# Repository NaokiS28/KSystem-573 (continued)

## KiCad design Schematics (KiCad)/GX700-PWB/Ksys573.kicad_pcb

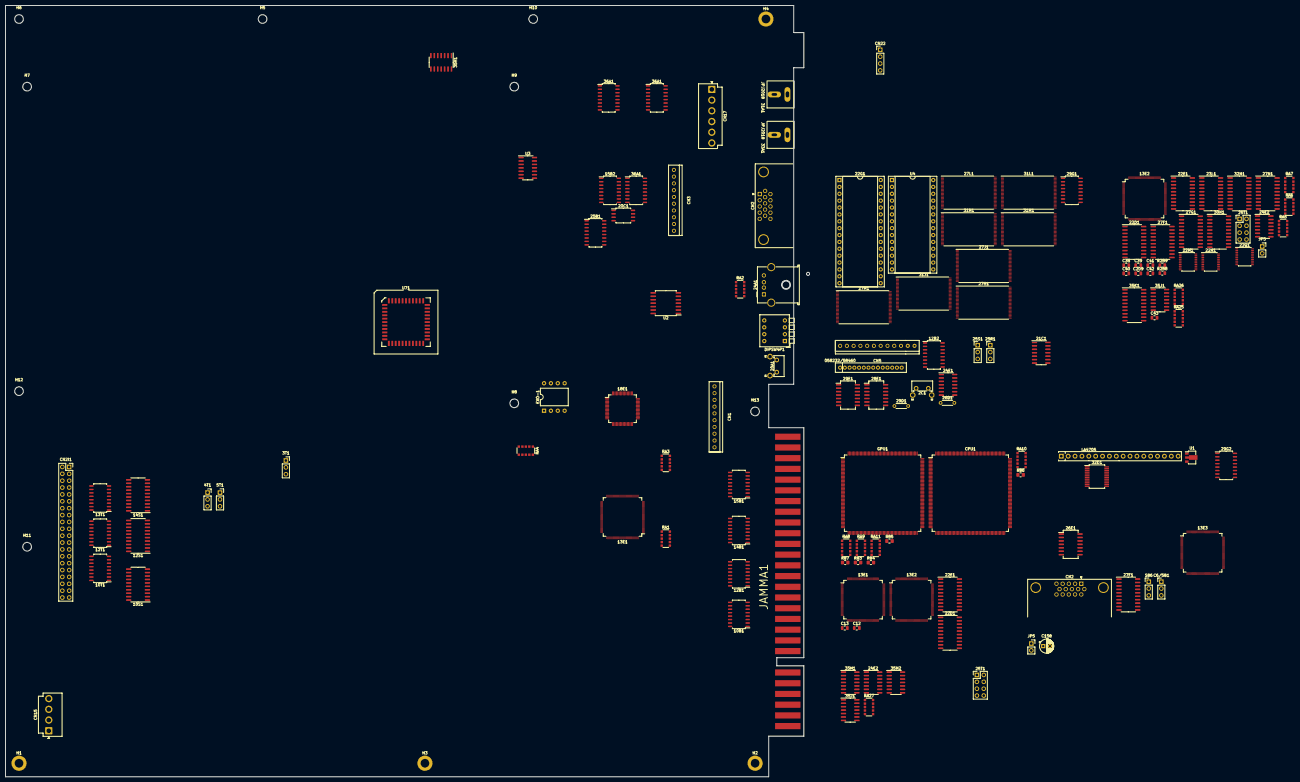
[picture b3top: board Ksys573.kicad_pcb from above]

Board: 4 copper layers, 295.0 x 285.0 mm, 145 parts (0 on the bottom side), 416 nets, no tracks yet.

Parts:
2C1: EVQ-PC1; SW_Tactile_SPST_Angled_PTS645Vx58-2LFS
3T1, 4T1, 5T1: EMI_Filter_LCL; PinSocket_1x03_P2.54mm_Vertical
10B1, 10T1, 12B1, 12B2, 12T1, 13T1, 14B1, 15B1, 15B2, 25B1, 36A1, 36A1#2, 36A1#3: ZBDS5101-8PT; SOIC-16_4.55x10.3mm_P1.27mm
10S1, 12S1, 14S1: 74LS245; SO-20_5.3x12.6mm_P1.27mm
13E1, 13E1#2, 13E2, 13E2#2, 13E3: KONAMI_056879; TQFP-120_14x14mm_P0.4mm
18E1: HD6433640; TQFP-64_10x10mm_P0.5mm
20A1: SW_Push; SW_Tactile_SPST_Angled_PTS645Vx58-2LFS
20C1: MAX485E; SOIC-8_5.23x5.23mm_P1.27mm
21C1, 35J1#2: 74LS74; SO-14_3.9x8.65mm_P1.27mm
22D1, 22D1#2, 22E1, 22E1#2, 27F1, 27F1#2, 27G1, 35K1: 74LS273; SO-20_5.3x12.6mm_P1.27mm
22G1: 27C040; DIP-32_W15.24mm_Socket
22M1, 22N1, 22Q1: 74LCX245; SSOP-20_4.4x6.5mm_P0.65mm
23L1, 27N1, 30N1, 32N1: 74F245; SO-20_5.3x12.6mm_P1.27mm
24A1: USB_A; USB_A_Molex_67643_Horizontal
24E1, 24E2, 24E2#2: 74LS14; SO-14_3.9x8.65mm_P1.27mm
25R1: U102; PinHeader_1x03_P2.54mm_Vertical
25S1: U101; PinHeader_1x03_P2.54mm_Vertical
25T1, 25T1#2: S240; PinHeader_2x04_P2.54mm_Vertical
26D1, 29D1: ZBF503D-00; R_Axial_DIN0204_L3.6mm_D1.6mm_P5.08mm_Horizontal
26E1: 74LS74; SO-14_5.3x10.2mm_P1.27mm
27H1, 27J1, 27L1, 27M1, 31H1, 31J1, 31L1, 31M1: 29F016-TSOP-SP; TSOP-I-48_18.4x12mm_P0.5mm
28E1, 29E1: 74LS07; SO-14_5.3x10.2mm_P1.27mm
29G1, 29G2: 74LS139; SOIC-16_4.55x10.3mm_P1.27mm
31A1: LINE L-OUT; RCA
32D1: SM5877AM; SSOP-24_5.3x8.2mm_P0.65mm
33A1: LINE R-OUT; RCA
35H1, 35H1#2, 35H2, 35J1: 74LS125; SO-14_3.9x8.65mm_P1.27mm
058232/58460: KONAMI-058232; KONAMI-SIP-14
C6/5B1: EMI222; PinHeader_1x03_P2.54mm_Vertical
C12, C13, C38, C39, C40, C41, C42, C43, C209: 10n; C_0805_2012Metric
C158: 10M16E; CP_Radial_D5.0mm_P2.50mm
CN1, CN3: B10PSHF1A; JST_NH_B10P_SHD
CN2, CN2#2: VGA-DSUB15; DSUB-15-HD_Female_Horizontal_P2.29x1.98mm_EdgePinOffset8.35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
CN2I1: ATA-IDE; PinSocket_2x20_P2.54mm_Vertical
CN5: B12PSHF1A; JST_NH_B12P_SHD
CN15: B4P-VH; JST_VH_B4P-VH-B_1x04_P3.96mm_Vertical
CN17: B6P-VH; JST_VH_B6P-VH-B_1x06_P3.96mm_Vertical
CN22: BS4PSHF1AA; PinHeader_1x04_P2.54mm_Vertical
CPU1: CXD8530CQ; LQFP-208_28x28mm_P0.5mm
DIPSW4P1: SW_DIP_x04; SW_DIP_SPSTx04_Piano_10.8x11.72mm_W7.62mm_P2.54mm
EXO-1: 14.7456MHz; DIP-8_W10.16mm
GPU1: CXD8561CQ; LQFP-208_28x28mm_P0.5mm
H1, H2, H3, H4: MountingHole_Pad; MountingHole_3.2mm_M3_DIN965_Pad
H5, H6, H7, H8, H9, H10, H11, H12, H13: MountingHole; MountingHole_3.2mm_M3
JAMMA1: JAMMA
JP5, JP5#2: Jumper_NO_Small; PinSocket_1x02_P2.54mm_Vertical
LA4705: LA4705; SIP18_Housing
R83, R84, R85, R86, R87: 220; R_0805_2012Metric_Pad1.20x1.40mm_HandSolder
R288: 100; R_0805_2012Metric
R289: 470; R_0805_2012Metric
RA1, RA2, RA3, RA4: 2.2k; R_Array_Convex_5x1206
RA5, RA6, RA7, RA25, RA26, RA27: 4.7k; R_Array_Convex_5x1206
RA8, RA9, RA10, RA11: 472; R_Array_Convex_5x1206
S86: Conn_01x03; PinHeader_1x03_P2.54mm_Vertical
U1: L78L05_SOT89; SOT-89-3
U2: ADC0834; SOIC-14W_7.5x9mm_P1.27mm
U3: 74LS74; SO-14_3.9x8.65mm_P1.27mm
U4: M48T58Y; DIP-28_W15.24mm_Socket
U71: 22J-X700A1 XC9536; PLCC-44_SMD-Socket

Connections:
13E-59: 13E1.59, 13E1#2.59
13E-PIN17: 13E1.17, 13E3.17
18E-17: 13E1.49, 13E1#2.49, 18E1.17 (P60)
18E-18: 13E1.50, 13E1#2.50, 18E1.18 (P61)
18E-34: 18E1.34 (P73), 21C1.5 (Q)
18E-35: 13E3.95, 18E1.35 (P74/TMRIV), 21C1.9 (Q)
18E-36: 13E3.96, 18E1.36 (P75/TMCIV)
18E-54: 18E1.54 (P14/PWM), 21C1.11 (C)
21C-1: 18E1.53 (P10/TMOW), 21C1.1 (~R)
22D-2: 18E1.39 (P80/FTCI), 22D1.2, 22D1#2.2 (Q0)
22D-5: 18E1.40 (P81/FTOA), 22D1.5, 22D1#2.5 (Q1)
22D-6: 18E1.41 (P82/FTOB), 22D1.6, 22D1#2.6 (Q2)
22D-9: 18E1.42 (P83/FTIA), 22D1.9, 22D1#2.9 (Q3)
22D-12: 18E1.43 (P84/FTIB), 22D1.12, 22D1#2.12 (Q4)
22D-15: 18E1.44 (P85/FTIC), 22D1.15, 22D1#2.15 (Q5)
22D-16: 18E1.45 (P86/FTID), 22D1.16, 22D1#2.16 (Q6)
22D-19: 18E1.46 (P87), 22D1.19, 22D1#2.19 (Q7)
22E-2: 18E1.1 (PB1/AN1), 22E1.2, 22E1#2.2 (Q0)
22E-5: 18E1.2 (PB0/AN0), 22E1.5, 22E1#2.5 (Q1)
22E-6: 18E1.64 (PB2/AN2), 22E1.6, 22E1#2.6 (Q2)
22E-9: 18E1.63 (PB3/AN3), 22E1.9, 22E1#2.9 (Q3)
22E-12: 18E1.62 (PB4/AN4), 22E1.12, 22E1#2.12 (Q4)
22E-15: 18E1.61 (PB5/AN5), 22E1.15, 22E1#2.15 (Q5)
22E-16: 18E1.60 (PB6/AN6), 22E1.16, 22E1#2.16 (Q6)
22E-19: 18E1.59 (PB7/AN7), 22E1.19, 22E1#2.19 (Q7)
22M-13: 25T1.4, 25T1.5, 25T1#2.4, 25T1#2.5
24E-13: 24E2.13, 24E2#2.13, 27G1.16 (Q6)
25T-6: 25T1.3, 25T1.6
25T-7: 25T1.2, 25T1.7
25T-8: 25T1.1, 25T1.8
27G-2: 27G1.2 (Q0), 29G1.14
27G-5: 27G1.5 (Q1), 29G1.13
27G-12: 27G1.12 (Q4), 29G1.2, 29G2.2 (A0)
27G-15: 27G1.15 (Q5), 29G1.3, 29G2.3 (A1)
29G-5: 29G1.5, 29G2.5 (O1)
29G-6: 25R1.2, 25R1.3, 29G1.6, 29G2.6 (O2)
35J-5: 13E3.97, 35J1#2.5 (Q)
35J-9: 13E3.98, 35J1#2.9 (Q), RA26.6 (R5)
058232-4: 13E1.83, 13E3.84, 058232/58460.4 (CC-IN2)
058232-5: 13E1.84, 13E3.85, 058232/58460.5 (CC-IN1)
+3V3: 22M1.20 (VCC), 22N1.20 (VCC), 22Q1.20 (VCC), RA8.5 (common), RA8.10 (common), RA9.5 (common), RA9.10 (common), RA10.5 (common), RA10.10 (common), RA11.5 (common), RA11.10 (common)
+5V: 13E1.16, 13E1.46, 13E1.60, 13E1.85, 13E1.120, 13E2.106, 22D1.20, 22E1.20, 27F1.20, 35J1.12, C41.1, C42.1
+12V: 3T1.1, 058232/58460.1 (COINC-FB), CN17.5, CN17.6
/IDE/IDE-A0: 13T1.14, CN2I1.35
/IDE/IDE-A1: 13T1.12, CN2I1.33
/IDE/IDE-A2: 13T1.13, CN2I1.36
/IDE/IDE-D0: 12T1.10, CN2I1.17
/IDE/IDE-D1: 12T1.12, CN2I1.15
/IDE/IDE-D2: 12T1.14, CN2I1.13
/IDE/IDE-D3: 12T1.16, CN2I1.11
/IDE/IDE-D4: 10T1.10, CN2I1.9
/IDE/IDE-D5: 10T1.12, CN2I1.7
/IDE/IDE-D6: 10T1.14, CN2I1.5
/IDE/IDE-D7: 10T1.16, CN2I1.3
/IDE/IDE-D8: 10T1.15, CN2I1.4
/IDE/IDE-D9: 10T1.13, CN2I1.6
/IDE/IDE-D10: 10T1.11, CN2I1.8
/IDE/IDE-D11: 10T1.9, CN2I1.10
/IDE/IDE-D12: 12T1.15, CN2I1.12
/IDE/IDE-D13: 12T1.13, CN2I1.14
/IDE/IDE-D14: 12T1.11, CN2I1.16
/IDE/IDE-D15: 12T1.9, CN2I1.18
/IDE/IDE-READ: 13T1.11, CN2I1.25
/IDE/IDE-WRITE: 13T1.10, CN2I1.23
/IO-DATA-0: 13E1.62, 22E1.3, 27F1.3
/IO-DATA-1: 13E1.63, 22E1.4, 27F1.4
/IO-DATA-2: 13E1.64, 22E1.7, 27F1.7
/IO-DATA-3: 13E1.65, 22E1.8, 27F1.8
/IO-DATA-4: 13E1.66, 22E1.13, 27F1.13
/IO-DATA-5: 13E1.67, 22E1.14, 27F1.14
/IO-DATA-6: 13E1.68, 22E1.17, 27F1.17
/IO-DATA-7: 13E1.69, 22E1.18, 27F1.18
/IO-DATA-8: 13E1.10, 22D1.3
/IO-DATA-9: 13E1.72, 22D1.4
/IO-DATA-10: 13E1.73, 22D1.7
/IO-DATA-11: 13E1.74, 22D1.8
/IO-DATA-12: 13E1.75, 22D1.13
/IO-DATA-13: 13E1.76, 22D1.14
/IO-DATA-14: 13E1.77, 22D1.17
/IO-DATA-15: 13E1.78, 22D1.18
/PCCARD (PCMCIA)/IO-AD-0: 25S1.2, 25S1.3
/ROM/IO-ADDR-0: 22G1.12 (A0), 27H1.30 (A0), 27J1.30 (A0), 27L1.30 (A0), 27M1.30 (A0), 31H1.30 (A0), 31J1.30 (A0), 31L1.30 (A0), 31M1.30 (A0)
/ROM/IO-ADDR-1: 22G1.11 (A1), 27H1.29 (A1), 27J1.29 (A1), 27L1.29 (A1), 27M1.29 (A1), 31H1.29 (A1), 31J1.29 (A1), 31L1.29 (A1), 31M1.29 (A1)
/ROM/IO-ADDR-2: 22G1.10 (A2), 27H1.28 (A2), 27J1.28 (A2), 27L1.28 (A2), 27M1.28 (A2), 31H1.28 (A2), 31J1.28 (A2), 31L1.28 (A2), 31M1.28 (A2)
/ROM/IO-ADDR-3: 22G1.9 (A3), 27H1.27 (A3), 27J1.27 (A3), 27L1.27 (A3), 27M1.27 (A3), 31H1.27 (A3), 31J1.27 (A3), 31L1.27 (A3), 31M1.27 (A3)
/ROM/IO-ADDR-4: 22G1.8 (A4), 27H1.22 (A4), 27J1.22 (A4), 27L1.22 (A4), 27M1.22 (A4), 31H1.22 (A4), 31J1.22 (A4), 31L1.22 (A4), 31M1.22 (A4)
/ROM/IO-ADDR-5: 22G1.7 (A5), 27H1.21 (A5), 27J1.21 (A5), 27L1.21 (A5), 27M1.21 (A5), 31H1.21 (A5), 31J1.21 (A5), 31L1.21 (A5), 31M1.21 (A5)
/ROM/IO-ADDR-6: 22G1.6 (A6), 27H1.20 (A6), 27J1.20 (A6), 27L1.20 (A6), 27M1.20 (A6), 31H1.20 (A6), 31J1.20 (A6), 31L1.20 (A6), 31M1.20 (A6)
/ROM/IO-ADDR-7: 22G1.5 (A7), 27H1.19 (A7), 27J1.19 (A7), 27L1.19 (A7), 27M1.19 (A7), 31H1.19 (A7), 31J1.19 (A7), 31L1.19 (A7), 31M1.19 (A7)
/ROM/IO-ADDR-8: 22G1.27 (A8), 27H1.18 (A8), 27J1.18 (A8), 27L1.18 (A8), 27M1.18 (A8), 31H1.18 (A8), 31J1.18 (A8), 31L1.18 (A8), 31M1.18 (A8)
/ROM/IO-ADDR-9: 22G1.26 (A9), 27H1.17 (A9), 27J1.17 (A9), 27L1.17 (A9), 27M1.17 (A9), 31H1.17 (A9), 31J1.17 (A9), 31L1.17 (A9), 31M1.17 (A9)
/ROM/IO-ADDR-10: 22G1.23 (A10), 27H1.16 (A10), 27J1.16 (A10), 27L1.16 (A10), 27M1.16 (A10), 31H1.16 (A10), 31J1.16 (A10), 31L1.16 (A10), 31M1.16 (A10)
/ROM/IO-ADDR-11: 22G1.25 (A11), 27H1.15 (A11), 27J1.15 (A11), 27L1.15 (A11), 27M1.15 (A11), 31H1.15 (A11), 31J1.15 (A11), 31L1.15 (A11), 31M1.15 (A11)
/ROM/IO-ADDR-12: 22G1.4 (A12), 27H1.10 (A12), 27J1.10 (A12), 27L1.10 (A12), 27M1.10 (A12), 31H1.10 (A12), 31J1.10 (A12), 31L1.10 (A12), 31M1.10 (A12)
/ROM/IO-ADDR-13: 22G1.28 (A13), 27H1.9 (A13), 27J1.9 (A13), 27L1.9 (A13), 27M1.9 (A13), 31H1.9 (A13), 31J1.9 (A13), 31L1.9 (A13), 31M1.9 (A13)
/ROM/IO-ADDR-14: 22G1.29 (A14), 27H1.8 (A14), 27J1.8 (A14), 27L1.8 (A14), 27M1.8 (A14), 31H1.8 (A14), 31J1.8 (A14), 31L1.8 (A14), 31M1.8 (A14)
/ROM/IO-ADDR-15: 22G1.3 (A15), 27H1.7 (A15), 27J1.7 (A15), 27L1.7 (A15), 27M1.7 (A15), 31H1.7 (A15), 31J1.7 (A15), 31L1.7 (A15), 31M1.7 (A15)
/ROM/IO-ADDR-16: 22G1.2 (A16), 27H1.6 (A16), 27J1.6 (A16), 27L1.6 (A16), 27M1.6 (A16), 31H1.6 (A16), 31J1.6 (A16), 31L1.6 (A16), 31M1.6 (A16)
/ROM/IO-ADDR-17: 22G1.30 (A17), 27H1.5 (A17), 27J1.5 (A17), 27L1.5 (A17), 27M1.5 (A17), 31H1.5 (A17), 31J1.5 (A17), 31L1.5 (A17), 31M1.5 (A17)
/ROM/IO-ADDR-18: 22G1.31 (A18), 27H1.4 (A18), 27J1.4 (A18), 27L1.4 (A18), 27M1.4 (A18), 31H1.4 (A18), 31J1.4 (A18), 31L1.4 (A18), 31M1.4 (A18)
/ROM/IO-ADDR-19: 27H1.3 (A19), 27J1.3 (A19), 27L1.3 (A19), 27M1.3 (A19), 31H1.3 (A19), 31J1.3 (A19), 31L1.3 (A19), 31M1.3 (A19)
/ROM/IO-ADDR-20: 27H1.46 (A20), 27J1.46 (A20), 27L1.46 (A20), 27M1.46 (A20), 31H1.46 (A20), 31J1.46 (A20), 31L1.46 (A20), 31M1.46 (A20)
/ROM/IO-DATA-0: 22G1.13 (D0), 31H1.31 (D0), 31J1.31 (D0), 31L1.31 (D0), 31M1.31 (D0), U4.11 (DQ0)
/ROM/IO-DATA-1: 22G1.14 (D1), 31H1.32 (D1), 31J1.32 (D1), 31L1.32 (D1), 31M1.32 (D1), U4.12 (DQ1)
/ROM/IO-DATA-2: 22G1.15 (D2), 31H1.33 (D2), 31J1.33 (D2), 31L1.33 (D2), 31M1.33 (D2), U4.13 (DQ2)
/ROM/IO-DATA-3: 22G1.17 (D3), 31H1.34 (D3), 31J1.34 (D3), 31L1.34 (D3), 31M1.34 (D3), U4.15 (DQ3)
/ROM/IO-DATA-4: 22G1.18 (D4), 31H1.38 (D4), 31J1.38 (D4), 31L1.38 (D4), 31M1.38 (D4), U4.16 (DQ4)
/ROM/IO-DATA-5: 22G1.19 (D5), 31H1.39 (D5), 31J1.39 (D5), 31L1.39 (D5), 31M1.39 (D5), U4.17 (DQ5)
/ROM/IO-DATA-6: 22G1.20 (D6), 31H1.40 (D6), 31J1.40 (D6), 31L1.40 (D6), 31M1.40 (D6), U4.18 (DQ6)
/ROM/IO-DATA-7: 22G1.21 (D7), 31H1.41 (D7), 31J1.41 (D7), 31L1.41 (D7), 31M1.41 (D7), U4.19 (DQ7)
/ROM/IO-DATA-8: 27H1.31 (D0), 27J1.31 (D0), 27L1.31 (D0), 27M1.31 (D0)
/ROM/IO-DATA-9: 27H1.32 (D1), 27J1.32 (D1), 27L1.32 (D1), 27M1.32 (D1)
/ROM/IO-DATA-10: 27H1.33 (D2), 27J1.33 (D2), 27L1.33 (D2), 27M1.33 (D2)
/ROM/IO-DATA-11: 27H1.34 (D3), 27J1.34 (D3), 27L1.34 (D3), 27M1.34 (D3)
/ROM/IO-DATA-12: 27H1.38 (D4), 27J1.38 (D4), 27L1.38 (D4), 27M1.38 (D4)
/ROM/IO-DATA-13: 27H1.39 (D5), 27J1.39 (D5), 27L1.39 (D5), 27M1.39 (D5)
/ROM/IO-DATA-14: 27H1.40 (D6), 27J1.40 (D6), 27L1.40 (D6), 27M1.40 (D6)
/ROM/IO-DATA-15: 27H1.41 (D7), 27J1.41 (D7), 27L1.41 (D7), 27M1.41 (D7)
/Security Cart/CART-7.37MHz: 35H1.3, 35H1#2.3
/Security Cart/CART-RTS: 35H1.11, 35H1#2.11
ADC-CLK: 13E1.80, 13E3.83, U2.12 (CLK)
ADC-DIN: 13E1.79, 13E3.79, U2.13 (DIN)
ADC-DOUT: 13E1.89, 13E3.89, U2.10 (DOUT)
ADC-SARS: 13E1.92, 13E3.80, 13E3.92, U2.11 (SARS)
ADC-~CS: 13E1.82, 13E3.82, U2.2 (~CS)
BUS-~RD: 10S1.1 (A->B), 12S1.1 (A->B), U4.22 (~OE), U71.18 (M13)
BUS-~WR: 27H1.44 (~WE), 27J1.44 (~WE), 27L1.44 (~WE), 27M1.44 (~WE), 31H1.44 (~WE), 31J1.44 (~WE), 31L1.44 (~WE), 31M1.44 (~WE), U4.27 (~WR), U71.25 (M17)
CART-20: 35H1.9, 35H2.9, 35K1.2 (Q0), RA25.9 (R8)
CART-29: 35J1#2.3 (C), RA26.4 (R4)
CART-30: 35J1.13, 35J1#2.13 (~R), RA26.7 (R6)
CART-33: 13E2.38, 13E2#2.38, RA27.1 (R1)
CART-34: 13E2.37, 13E2#2.37, RA27.2 (R2)
CART-35: 13E2.36, 13E2#2.36, RA27.3 (R3)
CART-36: 13E2.35, 13E2#2.35, RA27.4 (R4)
CART-37: 13E2.34, 13E2#2.34, RA27.9 (R8)
CART-38: 13E2.33, 13E2#2.33, RA27.8 (R7)
CART-39: 13E2.32, 13E2#2.32, RA27.7 (R6)
CART-40: 13E1.30, 13E1#2.30, RA27.6 (R5)
CN21-B6: 23L1.17 (B1), JP5.1, JP5#2.1
COIN1IN: 13E1.6, 13E3.6, RA1.2 (R2)
COIN2IN: 13E1.7, 13E3.7, RA1.8 (R7)
COIN-CNT1: 10B1.16, 058232/58460.3 (CC-OUT1)
COIN-CNT2: 10B1.15, 058232/58460.2 (CC-OUT2)
DAC-MUTE: 13E1.87, 13E3.87
DIP-1: 13E1.22, 13E1#2.22, DIPSW4P1.8
DIP-2: 13E1.23, 13E1#2.23, DIPSW4P1.7
DIP-3: 13E1.24, 13E1#2.24, DIPSW4P1.6
DIP-4: 13E1.25, 13E1#2.25, DIPSW4P1.5
DREQ5: 22M1.12 (B6), 25T1#2.3, 25T1#2.6
EXO-CLK: 18E1.8 (OSC1), 35H1.2, 35H1#2.2, EXO-1.2 (D)
EXP-A10: 13E1.90, 22D1.1, 22E1.1
EXT-OUT-LATCH: 27F1#2.11 (Cp), U71.43 (M4)
FLASH-CE0: 27H1.11 (~CE), 29G1.9, 31H1.11 (~CE)
FLASH-CE1: 27J1.11 (~CE), 29G1.10, 31J1.11 (~CE)
FLASH-CE2: 29G1.11, 31L1.11 (~CE)
FLASH-CE3: 27M1.11 (~CE), 29G1.12, 31M1.11 (~CE)
GND: 2C1.2, 3T1.2, 4T1.1, 4T1.2, 5T1.2, 10B1.13, 10S1.10 (GND), 12S1.10 (GND), 13E1.1, 13E1.11, 13E1.21, 13E1.41, 13E1.61, 13E1.71, 13E1.81, 13E1.91, 13E1.111, 13E1#2.21, 13E1#2.41, 13E1#2.51, 13E2.31, 13E2.101, 13E2#2.31, 13E3.1, 13E3.11, 13E3.61, 13E3.71, 13E3.81, 13E3.91, 13E3.101, 13E3.111, 14S1.10 (GND), 14S1.19 (CE), 15B1.9, 15B1.13, 15B2.9, 15B2.13, 18E1.3 (AVSS), 18E1.4 (TEST), 18E1.5 (X2), 18E1.7 (VSS), 20A1.2, 20C1.5 (GND), 22D1.10, 22D1#2.10 (GND), 22E1.10, 22E1#2.10 (GND), 22G1.16 (GND), 22G1.22 (~CE), 22M1.1 (A->B), 22M1.10 (GND), 22M1.17 (B1), 22M1.18 (B0), 22M1.19 (CE), 22N1.10 (GND), 22Q1.10 (GND), 23L1.10 (GND), 23L1.19 (CE), 25B1.9, 25B1.12, 25B1.16, 27F1.10, 27F1#2.10 (GND), 27G1.10 (GND), 27H1.35 (GND), 27H1.36 (GND), 27J1.35 (GND), 27J1.36 (GND), 27L1.35 (GND), 27L1.36 (GND), 27M1.35 (GND), 27M1.36 (GND), 27N1.10 (GND), 27N1.19 (CE), 29D1.1, 30N1.10 (GND), 30N1.19 (CE), 31H1.35 (GND), 31H1.36 (GND), 31J1.35 (GND), 31J1.36 (GND), 31L1.35 (GND), 31L1.36 (GND), 31M1.35 (GND), 31M1.36 (GND), 32N1.10 (GND), 32N1.19 (CE), 35H1.1, 35H1.4, 35H1.13, 35H1#2.1, 35H1#2.4, 35H1#2.13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
H8-TX-FLAG: 21C1.3 (C), U71.39 (I/O/GSR)
IDE-CS0: 13T1.15, 14S1.8 (A6), CN2I1.37, U71.2 (M1)
IDE-CS1: 13T1.16, 14S1.9 (A7), CN2I1.38, U71.3 (M2)
IDE-~RST: 14S1.2 (A0), 26E1.5 (Q)
IO-ADDR-0: 32N1.18 (B0), RA5.6 (R5)
IO-ADDR-1: 13E2.103, 13E3.103, 14S1.7 (A5), 32N1.17 (B1), RA5.4 (R4)
IO-ADDR-2: 13E2.104, 13E3.104, 14S1.5 (A3), 32N1.16 (B2), RA5.7 (R6)
IO-ADDR-3: 13E2.105, 13E3.105, 14S1.6 (A4), 32N1.15 (B3), RA5.3 (R3)
IO-ADDR-4: 32N1.14 (B4), RA5.8 (R7)
IO-ADDR-5: 32N1.13 (B5), RA5.2 (R2)
IO-ADDR-6: 32N1.12 (B6), RA5.9 (R8)
IO-ADDR-7: 32N1.11 (B7), RA5.1 (R1)
IO-ADDR-9: 30N1.17 (B1), RA6.4 (R4)
IO-ADDR-10: 5T1.1, 10S1.20 (VCC), 12S1.20 (VCC), 13E1#2.46, 13E1#2.60, 13E3.16, 13E3.99, 13E3.106, 13E3.120, 14S1.1 (A->B), 14S1.20 (VCC), 15B1.15, 15B1.16, 18E1.6 (X1), 18E1.33 (VCC), 18E1.58 (AVCC), 20C1.8 (VCC), 21C1.2 (D), 21C1.4 (~S), 21C1.10 (~S), 21C1.12 (D), 22D1#2.20 (VCC), 22E1#2.20 (VCC), 22G1.1 (VPP), 22G1.32 (VCC), 23L1.1 (A->B), 23L1.20 (VCC), 25B1.11, 26D1.1, 26E1.4 (~S), 26E1.10 (~S), 27F1#2.20 (VCC), 27G1.20 (VCC), 27H1.12 (VCC), 27H1.37 (VCC), 27J1.12 (VCC), 27J1.37 (VCC), 27L1.12 (VCC), 27L1.37 (VCC), 27M1.12 (VCC), 27M1.37 (VCC), 27N1.1 (A->B), 27N1.20 (VCC), 30N1.1 (A->B), 30N1.16 (B2), 30N1.18 (B0), 30N1.20 (VCC), 31H1.12 (VCC), 31H1.37 (VCC), 31J1.12 (VCC), 31J1.37 (VCC), 31L1.12 (VCC), 31L1.37 (VCC), 31M1.12 (VCC), 31M1.37 (VCC), 32N1.1 (A->B), 32N1.20 (VCC), 35J1#2.2 (D), 35J1#2.4 (~S), 35J1#2.10 (~S), 35J1#2.12 (D), 35K1.20 (VCC), C6/5B1.1, C12.1, C13.1, C38.1, C39.1, C40.1, C43.1, C209.1, CN1.1, CN1.2, CN3.1, CN3.2, CN17.1, CN17.2, CN22.3, EXO-1.3 (ST), EXO-1.8 (VCC), R289.1, RA1.5 (common), RA1.10 (common), RA2.5 (common), RA2.10 (common), RA3.5 (common), RA3.10 (common), RA4.5 (common), RA5.5 (common), RA5.10 (common), RA6.5 (common), RA6.6 (R5), RA6.7 (R6), RA6.10 (common)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
IO-ADDR-11: 30N1.15 (B3), RA6.3 (R3)
IO-ADDR-12: 30N1.14 (B4), RA6.8 (R7)
IO-ADDR-13: 30N1.13 (B5), RA6.2 (R2)
IO-ADDR-14: 30N1.12 (B6), RA6.9 (R8)
IO-ADDR-15: 30N1.11 (B7), RA6.1 (R1)
IO-ADDR-16: 27N1.18 (B0), RA7.6 (R5)
IO-ADDR-17: 27N1.17 (B1), RA7.4 (R4)
IO-ADDR-18: 27N1.16 (B2), RA7.7 (R6), U71.14 (M12)
IO-ADDR-19: 27N1.15 (B3), RA7.3 (R3), U71.13 (M11)
IO-ADDR-20: 27N1.14 (B4), RA7.8 (R7), U71.12 (M10)
IO-ADDR-21: 27N1.13 (B5), RA7.2 (R2), U71.11 (M9)
IO-ADDR-22: 27N1.12 (B6), RA7.9 (R8), U71.9 (M8)
IO-ADDR-23: 27N1.11 (B7), RA7.1 (R1), U71.8 (M6)
IO-DATA-0: 12S1.8 (A6), 13E3.62, 22N1.18 (B0), 26E1.2 (D), 27F1#2.3 (D0), 27G1.3 (D0), 35K1.3 (D0)
IO-DATA-1: 13E3.63, 22N1.17 (B1), 27F1#2.4 (D1), 27G1.4 (D1), 35K1.4 (D1)
IO-DATA-2: 13E3.64, 22N1.16 (B2), 27F1#2.7 (D2), 27G1.7 (D2), 35K1.7 (D2)
IO-DATA-3: 13E3.65, 22N1.15 (B3), 27F1#2.8 (D3), 27G1.8 (D3), 35K1.8 (D3)
IO-DATA-4: 13E3.66, 22N1.14 (B4), 27F1#2.13 (D4), 27G1.13 (D4), 35K1.13 (D4)
IO-DATA-5: 13E3.67, 22N1.13 (B5), 27F1#2.14 (D5), 27G1.14 (D5), 35K1.14 (D5)
IO-DATA-6: 13E3.68, 22N1.12 (B6), 27F1#2.17 (D6), 27G1.17 (D6), 35K1.17 (D6)
IO-DATA-7: 13E3.69, 22N1.11 (B7), 27F1#2.18 (D7), 27G1.18 (D7), 35K1.18 (D7)
IO-DATA-8: 13E3.10 (70), 22D1#2.3 (D0), 22Q1.18 (B0), 26E1.12 (D)
IO-DATA-9: 13E3.72, 22Q1.17 (B1)
IO-DATA-10: 13E3.73, 22Q1.16 (B2)
IO-DATA-11: 13E3.74, 22Q1.15 (B3)
IO-DATA-12: 13E3.75, 22Q1.14 (B4)
IO-DATA-13: 13E3.76, 22Q1.13 (B5)
IO-DATA-14: 13E3.77, 22Q1.12 (B6)
IO-DATA-15: 13E3.78, 22Q1.11 (B7)
J1-B4: 15B2.1, CN1.3, JAMMA1.A24 (P1_B4)
J1-B5: 15B2.2, CN1.4, JAMMA1.A25 (P1_B5)
J2-B4: 15B2.5, CN1.7, JAMMA1.B24 (P2_B4)
J2-B5: 15B2.7, CN1.9, JAMMA1.B25 (P2_B5)
JVS-RTS: 18E1.47 (P20/SCK3), 20C1.2 (~RE), 20C1.3 (DE)
JVS-RX: 18E1.48 (P21/RXD), 20C1.1 (RO)
JVS-S-IN: 13E1.94, 13E3.94, 18E1.11 (P90/FVPP), 24E1.10
JVS-SENSE: 24E1.9, 25B1.15
JVS-TX: 18E1.49 (P22/TXD), 20C1.4 (DI)
KCUS-93: 13E3.93, 35H2.8
LINE-L: 36A1.15, 36A1#2.15, 36A1#3.15
LINE-R: 36A1.13, 36A1#2.13, 36A1#3.13
LS273-~RST: 27F1.1, 27F1#2.1 (~Mr), 27G1.1 (~Mr)
unnamed: JAMMA1.A1 (GND), JAMMA1.A2 (GND), JAMMA1.A26 (GND), JAMMA1.A27 (GND), JAMMA1.B1 (GND), JAMMA1.B2 (GND), JAMMA1.B26 (GND), JAMMA1.B27 (GND)
unnamed: 3T1.3, CN15.1
unnamed: JAMMA1.A3 (+5V), JAMMA1.A4 (+5V), JAMMA1.B3 (+5V), JAMMA1.B4 (+5V)
unnamed: 4T1.3, CN15.2, CN15.3
unnamed: JAMMA1.A5 (-5V), JAMMA1.B5 (-5V)
unnamed: 5T1.3, CN15.4
unnamed: JAMMA1.A6 (+12V), JAMMA1.B6 (+12V)
unnamed: 10B1.1, JAMMA1.A7 (COIN_COUNT1)
unnamed: 10B1.2, JAMMA1.B7 (COIN_COUNT2)
unnamed: 10B1.4, JAMMA1.A13 (VIDEO-GND)
unnamed: 10B1.5, JAMMA1.A14 (TEST)
unnamed: 10B1.6, JAMMA1.B13 (SERVICE)
unnamed: 10B1.7, JAMMA1.A15 (COIN_1)
unnamed: 10B1.8, JAMMA1.B15 (COIN_2)
unnamed: 10S1.11 (B7), 10T1.8
unnamed: 10S1.12 (B6), 10T1.7
unnamed: 10S1.13 (B5), 10T1.6
unnamed: 10S1.14 (B4), 10T1.5
unnamed: 10S1.15 (B3), 10T1.4
unnamed: 10S1.16 (B2), 10T1.3
unnamed: 10S1.17 (B1), 10T1.2
unnamed: 10S1.18 (B0), 10T1.1
unnamed: 12B1.1, JAMMA1.A16 (P1_START)
unnamed: 12B1.2, JAMMA1.B16 (P2_START)
unnamed: 12B1.3, JAMMA1.A17 (P1_UP)
unnamed: 12B1.4, JAMMA1.B17 (P2_UP)
unnamed: 12B1.5, JAMMA1.A18 (P1_DOWN)
unnamed: 12B1.6, JAMMA1.B18 (P2_DOWN)
unnamed: 12B1.7, JAMMA1.A19 (P1_LEFT)
unnamed: 12B1.8, JAMMA1.B19 (P2_LEFT)
unnamed: 12B2.1, CN5.3
unnamed: 12B2.2, CN5.4
unnamed: 12B2.3, CN5.5
unnamed: 12B2.4, CN5.6
unnamed: 12B2.5, CN5.7
unnamed: 12B2.6, CN5.8
unnamed: 12B2.7, CN5.9
unnamed: 12B2.8, CN5.10
unnamed: 12B2.9, 29E1.2
unnamed: 12B2.10, 29E1.12
unnamed: 12B2.11, 28E1.8
unnamed: 12B2.12, 28E1.6
unnamed: 12B2.13, 28E1.10
unnamed: 12B2.14, 28E1.4
unnamed: 12B2.15, 28E1.12
unnamed: 12B2.16, 28E1.2
unnamed: 12S1.11 (B7), 12T1.8
unnamed: 12S1.12 (B6), 12T1.7
unnamed: 12S1.13 (B5), 12T1.6
unnamed: 12S1.14 (B4), 12T1.5
unnamed: 12S1.15 (B3), 12T1.4
unnamed: 12S1.16 (B2), 12T1.3
unnamed: 12S1.17 (B1), 12T1.2
unnamed: 12S1.18 (B0), 12T1.1
unnamed: 13E1.26, 13E1#2.26, 18E1.12 (P91)
unnamed: 13E1.27, 13E1#2.27, 18E1.13 (P92)
unnamed: 13E1.28, 13E1#2.28, 18E1.14 (P93)
unnamed: 13E1.29, 13E1#2.29, 18E1.15 (P94)
unnamed: 13E1.42, 13E1#2.42, 18E1.27 (P52/~INT2)
unnamed: 13E1.43, 13E1#2.43, 18E1.28 (P53/~INT3)
unnamed: 13E1.44, 13E1#2.44, 18E1.29 (P54/~INT4)
unnamed: 13E1.45, 13E1#2.45, 18E1.30 (P55/~INT5/~ADTRG)
unnamed: 13E1.47, 13E1#2.47, 18E1.31 (P56/~INT6/TMIB)
unnamed: 13E1.48, 13E1#2.48, 18E1.32 (P57/~INT7)
unnamed: 13E1.52, 13E1#2.52, 18E1.19 (P62)
unnamed: 13E1.53, 13E1#2.53, 18E1.20 (P63)
unnamed: 13E1.54, 13E1#2.54, 18E1.21 (P64)
unnamed: 13E1.55, 13E1#2.55, 18E1.22 (P65)
unnamed: 13E1.56, 13E1#2.56, 18E1.23 (P66)
unnamed: 13E1#2.57, 18E1.24 (P67)
unnamed: 13E1.93, 35H1.8
unnamed: 13E2#2.39, 18E1.25 (P50/~INT0)
unnamed: 13E2#2.40, 18E1.26 (P51/~INT1)
unnamed: 13T1.1, 14S1.11 (B7)
unnamed: 13T1.2, 14S1.12 (B6)
unnamed: 13T1.3, 14S1.13 (B5)
unnamed: 13T1.4, 14S1.14 (B4)
unnamed: 13T1.5, 14S1.15 (B3)
unnamed: 13T1.6, 14S1.16 (B2)
unnamed: 13T1.7, 14S1.17 (B1)
unnamed: 13T1.8, 14S1.18 (B0)
unnamed: 14B1.1, JAMMA1.A20 (P1_RIGHT)
unnamed: 14B1.2, JAMMA1.B20 (P21_RIGHT)
unnamed: 14B1.3, JAMMA1.A21 (P1_B1)
unnamed: 14B1.4, JAMMA1.B21 (P2_B1)
unnamed: 14B1.5, JAMMA1.A22 (P1_B2)
unnamed: 14B1.6, JAMMA1.B22 (P2_B2)
unnamed: 14B1.7, JAMMA1.A23 (P1_B3)
unnamed: 14B1.8, JAMMA1.B23 (P2_B3)
unnamed: 15B1.1, CN3.3
unnamed: 15B1.2, CN3.4
unnamed: 15B1.3, CN3.5
unnamed: 15B1.4, CN3.6
unnamed: 15B1.5, CN3.7
unnamed: 15B1.6, CN3.8
unnamed: 15B1.7, CN3.9
unnamed: 15B1.8, CN3.10
unnamed: 15B1.10, U2.6 (CH3)
unnamed: 15B1.11, U2.5 (CH2)
unnamed: 15B1.12, U2.4 (CH1)
unnamed: 15B1.14, U2.3 (CH0)
unnamed: 15B2.3, CN1.5
unnamed: 15B2.4, CN1.6
unnamed: 15B2.6, CN1.8
unnamed: 15B2.8, CN1.10
unnamed: 20C1.6 (A), 25B1.13
unnamed: 20C1.7 (B), 25B1.14
unnamed: 23L1.16 (B2), R288.1, R289.2
unnamed: 24A1.1 (VBUS), 25B1.2
unnamed: 24A1.2 (D-), 25B1.4
unnamed: 24A1.3 (D+), 25B1.3
unnamed: 24A1.4 (GND), 25B1.5
unnamed: 24A1.5 (Shield), 25B1.1
unnamed: 24E1.8, 24E1.11
unnamed: 24E2.12, 24E2#2.12, 35H1.10, 35H2.10
unnamed: 26D1.2, CN5.1, CN5.2
unnamed: 27F1#2.2 (Q0), 29E1.1
unnamed: 27F1#2.5 (Q1), 29E1.13
unnamed: 27F1#2.6 (Q2), 28E1.9
unnamed: 27F1#2.9 (Q3), 28E1.5
unnamed: 27F1#2.12 (Q4), 28E1.11
unnamed: 27F1#2.15 (Q5), 28E1.3
unnamed: 27F1#2.16 (Q6), 28E1.13
unnamed: 27F1#2.19 (Q7), 28E1.1
unnamed: 29D1.2, CN5.11, CN5.12
unnamed: 29G1.4, 29G1.15
unnamed: 31A1.1 (In), 36A1.2, 36A1#2.2, 36A1#3.2
unnamed: 31A1.2 (Ext), 36A1.1, 36A1#2.1, 36A1#3.1
unnamed: 32D1.11 (L_AVDD), 32D1.15 (R_AVDD)
unnamed: 33A1.1 (In), 36A1.4, 36A1#2.4, 36A1#3.4
unnamed: 33A1.2 (Ext), 36A1.3, 36A1#2.3, 36A1#3.3
unnamed: 36A1.5, 36A1#2.5, 36A1#3.5
unnamed: 36A1.6, 36A1#2.6, 36A1#3.6
unnamed: 36A1.7, 36A1#2.7, 36A1#3.7
unnamed: 36A1.8, 36A1#2.8, 36A1#3.8
unnamed: 058232/58460.8 (VCC), C6/5B1.3
unnamed: 058232/58460.10 (WD_RESET), S86.3
unnamed: 058232/58460.11 (WD_DISABLE), S86.1
unnamed: 2C1.1, 058232/58460.12 (~RESET_IN), C158.1
unnamed: CPU1.1 (3.3v), CPU1.2 (3.3v), CPU1.14 (3.3v), CPU1.26 (3.3v), CPU1.38 (3.3v), CPU1.50 (3.3v), CPU1.53 (3.3v), CPU1.54 (3.3v), CPU1.66 (3.3v), CPU1.79 (3.3v), CPU1.92 (3.3v), CPU1.103 (3.3v), CPU1.105 (3.3v), CPU1.106 (3.3v), CPU1.118 (3.3v), CPU1.131 (3.3v), CPU1.144 (3.3v), CPU1.157 (3.3v), CPU1.158 (3.3v), CPU1.171 (3.3v), CPU1.183 (3.3v), CPU1.196 (3.3v)
unnamed: CPU1.15 (GND), CPU1.27 (GND), CPU1.39 (GND), CPU1.51 (GND), CPU1.52 (GND), CPU1.65 (GND), CPU1.78 (GND), CPU1.91 (GND), CPU1.104 (GND), CPU1.117 (GND), CPU1.130 (GND), CPU1.143 (GND), CPU1.155 (GND), CPU1.156 (GND), CPU1.170 (GND), CPU1.182 (GND), CPU1.195 (GND), CPU1.207 (GND), CPU1.208 (GND)
unnamed: CPU1.202 (GPU-DACK), R83.1
unnamed: CPU1.203 (~GPU-WR), R87.1
unnamed: CPU1.204 (~GPU-RD), R86.1
unnamed: CPU1.205 (~GPU-CS), R85.1
unnamed: CPU1.206 (~DSYSCLK), R84.1
unnamed: GPU1.7 (3.3v), GPU1.10 (3.3v), GPU1.15 (3.3v), GPU1.22 (3.3v), GPU1.23 (3.3v), GPU1.29 (3.3v), GPU1.37 (3.3v), GPU1.43 (3.3v), GPU1.51 (3.3v), GPU1.61 (3.3v), GPU1.67 (3.3v), GPU1.71 (3.3v), GPU1.72 (3.3v), GPU1.73 (3.3v), GPU1.74 (3.3v), GPU1.75 (3.3v), GPU1.80 (3.3v), GPU1.87 (3.3v), GPU1.97 (3.3v), GPU1.106 (3.3v), GPU1.114 (3.3v), GPU1.120 (3.3v), GPU1.130 (3.3v), GPU1.133 (3.3v), GPU1.136 (3.3v), GPU1.141 (3.3v), GPU1.147 (3.3v), GPU1.151 (3.3v), GPU1.154 (3.3v), GPU1.165 (3.3v), GPU1.175 (3.3v), GPU1.185 (3.3v), GPU1.191 (3.3v), GPU1.193 (3.3v), GPU1.195 (3.3v), GPU1.197 (3.3v), GPU1.201 (3.3v), GPU1.205 (3.3v), GPU1.208 (3.3v)
unnamed: GPU1.8 (GND), GPU1.11 (GND), GPU1.16 (GND), GPU1.20 (GND), GPU1.30 (GND), GPU1.38 (GND), GPU1.44 (GND), GPU1.52 (GND), GPU1.60 (GND), GPU1.66 (GND), GPU1.76 (GND), GPU1.81 (GND), GPU1.88 (GND), GPU1.96 (GND), GPU1.105 (GND), GPU1.113 (GND), GPU1.119 (GND), GPU1.129 (GND), GPU1.132 (GND), GPU1.135 (GND), GPU1.142 (GND), GPU1.146 (GND), GPU1.152 (GND), GPU1.155 (GND), GPU1.164 (GND), GPU1.174 (GND), GPU1.184 (GND), GPU1.190 (GND), GPU1.194 (GND), GPU1.198 (GND), GPU1.200 (GND), GPU1.204 (GND), GPU1.207 (GND)
P1B1IN: 13E1.112, 13E3.112, RA2.4 (R4)
P1B5IN: 13E1.12, 13E3.12, RA3.3 (R3)
P1B6IN: 13E1.19, 13E3.19, RA3.4 (R4)
P1DNIN: 13E2.110, 13E3.110, RA2.1 (R1)
P1LFIN: 13E2.107, 13E3.107, RA2.2 (R2)
P1RTIN: 13E2.108, 13E3.108, RA2.3 (R3)
P1STARTIN: 13E1.115, 13E3.115, RA1.3 (R3)
P1UPIN: 13E2.109, 13E3.109, RA1.4 (R4)
P2B1IN: 13E1.2, 13E3.2, RA2.6 (R5)
P2B4IN: 13E1.13, 13E3.13, RA3.8 (R7)
P2B5: 13E1.14, 13E3.14
P2B6IN: 13E1.20, 13E3.20, RA3.6 (R5)
P2DNIN: 13E1.119, 13E3.119, RA2.9 (R8)
P2LFIN: 13E1.116, 13E3.116, RA2.8 (R7)
P2RTIN: 13E1.117, 13E3.117, RA2.7 (R6)
P2STARTIN: 13E1.5, 13E3.5, RA1.7 (R6)
P2UPIN: 13E1.118, 13E3.118, RA1.6 (R5)
PCMCIA1-IN: 13E1.8, 13E3.8
PCMCIA2-IN: 13E1.9, 13E3.9
PSX-TX1: 35H1.5, 35H1#2.5
PSX-~BIOS: 22G1.24 (~OE), U71.19 (M14)
PSX-~RTS: 35H1.12, 35H1#2.12
RTC-FT: 13E3.18, U4.1 (FT)
RTC-OE: U4.20 (~E1), U71.40 (I/O/GTS2)
SERVICEIN: 13E1.15, 13E3.15, RA1.9 (R8)
SPL+: 36A1.12, 36A1#2.12, 36A1#3.12, JAMMA1.A9 ((L)SP+)
SPL-: 36A1.11, 36A1#2.11, 36A1#3.11, JAMMA1.B9 ((L)SP-)
SPR+: 36A1.10, 36A1#2.10, 36A1#3.10
SPR-: 36A1.9, 36A1#2.9, 36A1#3.9
TEST: 10B1.12, 20A1.1
TESTBTN: 13E1.58, 13E1#2.58, RA1.1 (R1)
TX1: 35H1.6, 35H1#2.6, RA26.3 (R3)
U17-38: 35J1.11, 35K1.11 (Cp)
U17-39: 22D1.11, 22D1#2.11 (Cp), 22E1.11, 22E1#2.11 (Cp)
U71-5: 21C1.13 (~R), U71.5 (I/O/GCK1)
U71-7: 27G1.19 (Q7), U71.7 (I/O/GCK3)
U71-22: CN2I1.31, U71.22 (M16)
U71-24: 22M1.13 (B5), U71.24 (M17)
U71-26: 13E3.102, U71.26 (M16)
U71-27: 13E3.100, 26E1.11 (C), U71.27 (M15)
U71-34: 10S1.19 (CE), 12S1.19 (CE), U71.34 (M11)
U71-38: 35J1#2.11 (C), U71.38 (M7)
VGA-14: JP5.2, JP5#2.2
VGA-CSYNC: 25B1.7, R288.2
WD_KICK: 058232/58460.9 (WD-IN), CN22.1, U71.44 (M2)
~ATA-RST: 13T1.9, CN2I1.1
~BUS-RD: 14S1.4 (A2), 23L1.11 (B7), 27H1.43 (~OE), 27J1.43 (~OE), 27L1.43 (~OE), 27M1.43 (~OE), 31H1.43 (~OE), 31J1.43 (~OE), 31L1.43 (~OE), 31M1.43 (~OE)
~BUS-WR: 14S1.3 (A1), 23L1.12 (B6)
~DBUS-EN: 22N1.19 (CE), 22Q1.19 (CE), U71.35 (M10)
~EXP1: 25T1#2.2, 25T1#2.7, U71.28 (M14)
~EXP-CE: 23L1.14 (B4), U71.42 (I/O/GTS1)
~PCMCIA_CE1: 25R1.1, U71.33 (M12)
~PCMCIA_CE2: 29G2.1 (E), U71.37 (M8)
~PSX-RD: 22N1.1 (A->B), 22Q1.1 (A->B), 23L1.9 (A7)
~RESET: 13E3.90, 22D1#2.1 (~Mr), 22E1#2.1 (~Mr), 22M1.11 (B7), 25T1#2.1, 25T1#2.8, 26E1.1 (~R), 26E1.13 (~R), 27H1.14 (~RESET), 27J1.14 (~RESET), 27L1.14 (~RESET), 27M1.14 (~RESET), 31H1.14 (~RESET), 31J1.14 (~RESET), 31L1.14 (~RESET), 31M1.14 (~RESET), 35K1.1 (~Mr), 058232/58460.13 (~WD_RESET), CN22.2, U71.1 (M1)

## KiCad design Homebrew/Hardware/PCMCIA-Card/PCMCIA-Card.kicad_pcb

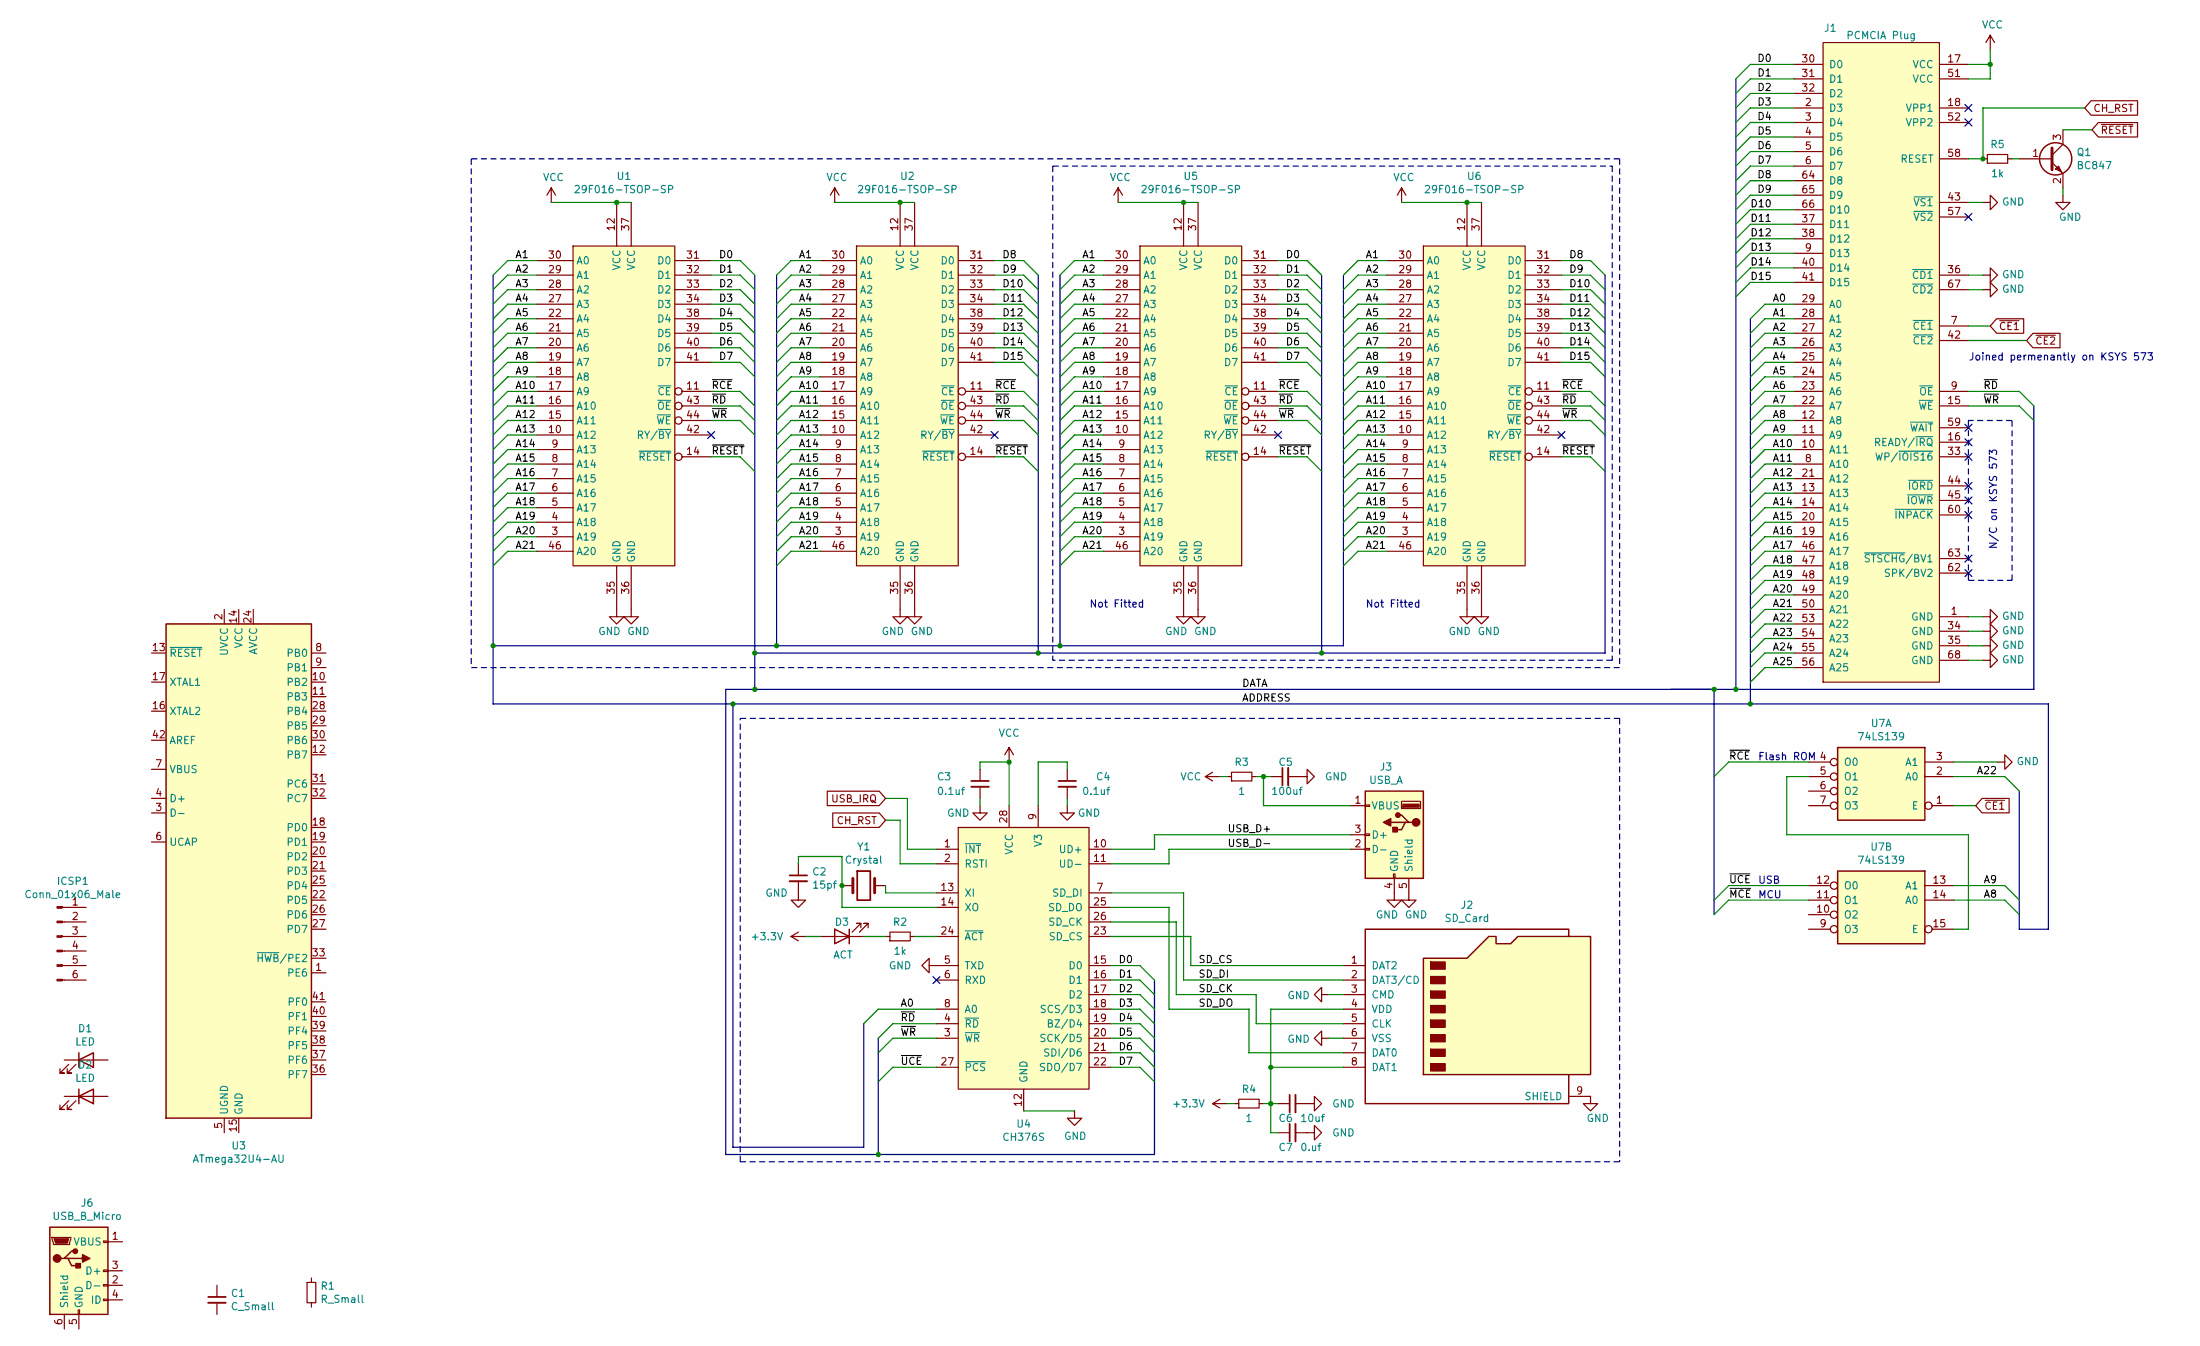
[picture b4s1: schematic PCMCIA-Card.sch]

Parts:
C1: C_Small; C_1206_3216Metric_Pad1.33x1.80mm_HandSolder
C2: 15pf; C_1206_3216Metric_Pad1.33x1.80mm_HandSolder
C3, C4: 0.1uf; C_1206_3216Metric_Pad1.33x1.80mm_HandSolder
C5: 100uf; C_1206_3216Metric_Pad1.33x1.80mm_HandSolder
C6: 10uf; C_1206_3216Metric_Pad1.33x1.80mm_HandSolder
C7: 0.uf; C_1206_3216Metric_Pad1.33x1.80mm_HandSolder
D1, D2: LED; LED_1206_3216Metric
D3: ACT; LED_1206_3216Metric
ICSP1: Conn_01x06_Male; PinHeader_2x03_P2.54mm_Vertical_SMD
J1: PCMCIA Plug; PCMCIA-Female
J2: SD_Card; microSD_HC_Hirose_DM3D-SF
J3: USB_A; USB_A_Molex_67643_Horizontal
J6: USB_B_Micro; USB_Micro-B_Wuerth_629105150521
Q1: BC847; SOT-23
R1: R_Small; R_1206_3216Metric_Pad1.30x1.75mm_HandSolder
R2, R5: 1k; R_1206_3216Metric_Pad1.30x1.75mm_HandSolder
R3, R4: 1; R_1206_3216Metric_Pad1.30x1.75mm_HandSolder
U1, U2, U5, U6: 29F016-TSOP-SP; TSOP-I-48_18.4x12mm_P0.5mm
U3: ATmega32U4-AU; TQFP-44_10x10mm_P0.8mm
U4: CH376S; SOIC-28W_7.5x17.9mm_P1.27mm
U7: 74LS139; SO-16_3.9x9.9mm_P1.27mm
Y1: Crystal; Crystal_SMD_5032-2Pin_5.0x3.2mm_HandSoldering

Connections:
+3V3: D3.2 (A), R4.1
/A0: J1.29 (A0), U4.8 (A0)
/A1: J1.28 (A1), U1.30 (A0), U2.30 (A0), U5.30 (A0), U6.30 (A0)
/A2: J1.27 (A2), U1.29 (A1), U2.29 (A1), U5.29 (A1), U6.29 (A1)
/A3: J1.26 (A3), U1.28 (A2), U2.28 (A2), U5.28 (A2), U6.28 (A2)
/A4: J1.25 (A4), U1.27 (A3), U2.27 (A3), U5.27 (A3), U6.27 (A3)
/A5: J1.24 (A5), U1.22 (A4), U2.22 (A4), U5.22 (A4), U6.22 (A4)
/A6: J1.23 (A6), U1.21 (A5), U2.21 (A5), U5.21 (A5), U6.21 (A5)
/A7: J1.22 (A7), U1.20 (A6), U2.20 (A6), U5.20 (A6), U6.20 (A6)
/A8: J1.12 (A8), U1.19 (A7), U2.19 (A7), U5.19 (A7), U6.19 (A7), U7.14 (A0)
/A9: J1.11 (A9), U1.18 (A8), U2.18 (A8), U5.18 (A8), U6.18 (A8), U7.13 (A1)
/A10: J1.10 (A11), U1.17 (A9), U2.17 (A9), U5.17 (A9), U6.17 (A9)
/A11: J1.8 (A10), U1.16 (A10), U2.16 (A10), U5.16 (A10), U6.16 (A10)
/A12: J1.21 (A12), U1.15 (A11), U2.15 (A11), U5.15 (A11), U6.15 (A11)
/A13: J1.13 (A13), U1.10 (A12), U2.10 (A12), U5.10 (A12), U6.10 (A12)
/A14: J1.14 (A14), U1.9 (A13), U2.9 (A13), U5.9 (A13), U6.9 (A13)
/A15: J1.20 (A15), U1.8 (A14), U2.8 (A14), U5.8 (A14), U6.8 (A14)
/A16: J1.19 (A16), U1.7 (A15), U2.7 (A15), U5.7 (A15), U6.7 (A15)
/A17: J1.46 (A17), U1.6 (A16), U2.6 (A16), U5.6 (A16), U6.6 (A16)
/A18: J1.47 (A18), U1.5 (A17), U2.5 (A17), U5.5 (A17), U6.5 (A17)
/A19: J1.48 (A19), U1.4 (A18), U2.4 (A18), U5.4 (A18), U6.4 (A18)
/A20: J1.49 (A20), U1.3 (A19), U2.3 (A19), U5.3 (A19), U6.3 (A19)
/A21: J1.50 (A21), U1.46 (A20), U2.46 (A20), U5.46 (A20), U6.46 (A20)
/A22: J1.53 (A22), U7.2 (A0)
/A23: J1.54 (A23)
/A24: J1.55 (A24)
/A25: J1.56 (A25)
/D0: J1.30 (D0), U1.31 (D0), U4.15 (D0), U5.31 (D0)
/D1: J1.31 (D1), U1.32 (D1), U4.16 (D1), U5.32 (D1)
/D2: J1.32 (D2), U1.33 (D2), U4.17 (D2), U5.33 (D2)
/D3: J1.2 (D3), U1.34 (D3), U4.18 (SCS/D3), U5.34 (D3)
/D4: J1.3 (D4), U1.38 (D4), U4.19 (BZ/D4), U5.38 (D4)
/D5: J1.4 (D5), U1.39 (D5), U4.20 (SCK/D5), U5.39 (D5)
/D6: J1.5 (D6), U1.40 (D6), U4.21 (SDI/D6), U5.40 (D6)
/D7: J1.6 (D7), U1.41 (D7), U4.22 (SDO/D7), U5.41 (D7)
/D8: J1.64 (D8), U2.31 (D0), U6.31 (D0)
/D9: J1.65 (D9), U2.32 (D1), U6.32 (D1)
/D10: J1.66 (D10), U2.33 (D2), U6.33 (D2)
/D11: J1.37 (D11), U2.34 (D3), U6.34 (D3)
/D12: J1.38 (D12), U2.38 (D4), U6.38 (D4)
/D14: J1.40 (D14), U2.40 (D6), U6.40 (D6)
/D15: J1.41 (D15), U2.41 (D7), U6.41 (D7)
/SD_CK: J2.5 (CLK), U4.26 (SD_CK)
/SD_CS: J2.1 (DAT2), U4.23 (SD_CS)
/SD_DI: J2.2 (DAT3/CD), U4.7 (SD_DI)
/SD_DO: J2.7 (DAT0), U4.25 (SD_DO)
/USB_D+: J3.3 (D+), U4.10 (UD+)
/USB_D-: J3.2 (D-), U4.11 (UD-)
/~MCE: U7.11 (O1)
/~RCE: U1.11 (~CE), U2.11 (~CE), U5.11 (~CE), U6.11 (~CE), U7.4 (O0)
/~UCE: U4.27 (~PCS), U7.12 (O0)
/~WR: J1.15 (~WE), U1.44 (~WE), U2.44 (~WE), U4.3 (~WR), U5.44 (~WE), U6.44 (~WE)
CH_RST: J1.58 (RESET), R5.1, U4.2 (RSTI)
unnamed: C2.1, U4.14 (XO), Y1.1
unnamed: C4.1, U4.9 (V3)
unnamed: C5.1, J3.1 (VBUS), R3.2
unnamed: C6.1, C7.1, J2.4 (VDD), J2.8 (DAT1), R4.2
unnamed: D3.1 (K), R2.1
unnamed: Q1.1 (B), R5.2
unnamed: R2.2, U4.24 (~ACT)
unnamed: U3.14 (VCC), U3.34 (VCC)
unnamed: U3.15 (GND), U3.23 (GND), U3.35 (GND), U3.43 (GND)
unnamed: U3.24 (AVCC), U3.44 (AVCC)
unnamed: U4.13 (XI), Y1.2
unnamed: U7.5 (O1), U7.15 (E)
USB_IRQ: U4.1 (~INT~)
VCC: C3.1, J1.17 (VCC), J1.51 (VCC), R3.1, U1.12 (VCC), U1.37 (VCC), U2.12 (VCC), U2.37 (VCC), U4.28 (VCC), U5.12 (VCC), U5.37 (VCC), U6.12 (VCC), U6.37 (VCC)
~CE1: J1.7 (~CE1), U7.1 (E)
~CE2: J1.42 (~CE2)
~RESET: Q1.3 (C), U1.14 (~RESET), U2.14 (~RESET), U5.14 (~RESET), U6.14 (~RESET)

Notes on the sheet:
MCU
USB
Flash ROM
Not Fitted
N/C on KSYS 573
Joined permenantly on KSYS 573

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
